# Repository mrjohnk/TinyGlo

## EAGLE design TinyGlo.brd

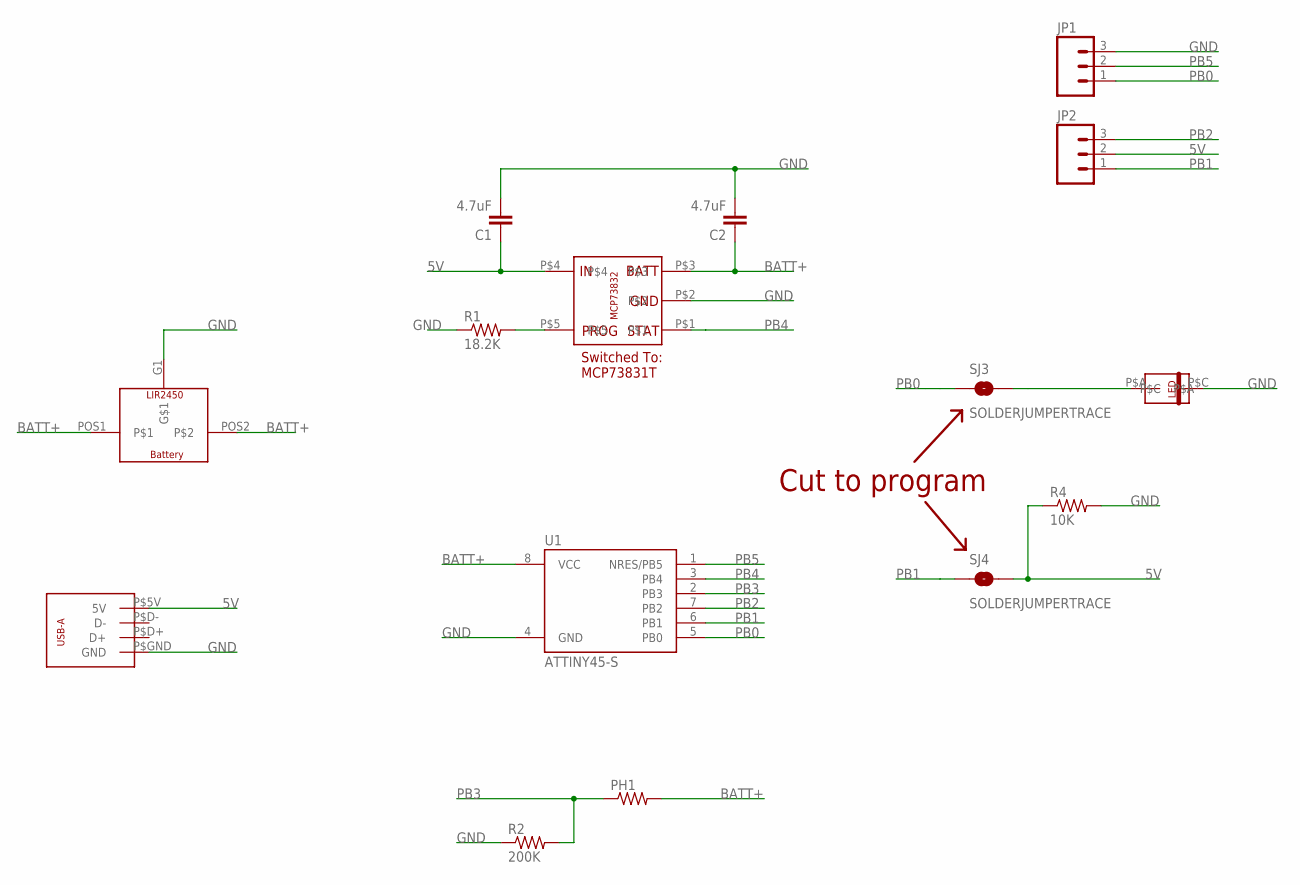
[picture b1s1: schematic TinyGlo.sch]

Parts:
C1, C2: 4.7uF; 0603-CAP
JP1, JP2: M03LOCK; 1X03_LOCK
PH1: RESISTOR0805-RES; 0805
R1: 18.2K; 0603-RES
R2: 200K; 0603-RES
R4: 10K; 0603-RES
SJ3, SJ4: SOLDERJUMPERTRACE; SJ_2S-TRACE
U1: ATTINY45-S; SOIC8_EIAJ_208MIL
U$1: LIPOBATTCHG-MCP73832T-2DFI/OT
U$2: LIR2450_SMD_BATT_BK-5033
U$3: USB-A_PCB_TRACES
U$4: PLCC-2_LED

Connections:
5V: C1.1, JP2.2, R4.1, SJ4.2, U$1.P$4, U$3.P$5V (5V)
BATT+: C2.1, PH1.2, U1.8 (VCC), U$1.P$3, U$2.POS1, U$2.POS2
GND: C1.2, C2.2, JP1.3, R1.1, R2.1, R4.2, U1.4 (GND), U$1.P$2, U$2.G1, U$3.P$GND (GND), U$4.P$C
unnamed: R1.2, U$1.P$5
unnamed: SJ3.2, U$4.P$A
PB0: JP1.1, SJ3.1, U1.5 (PB0)
PB1: JP2.1, SJ4.1, U1.6 (PB1)
PB2: JP2.3, U1.7 (PB2)
PB3: PH1.1, R2.2, U1.2 (PB3)
PB4: U1.3 (PB4), U$1.P$1
PB5: JP1.2, U1.1 (NRES/PB5)

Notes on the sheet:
Cut to program
Switched To: MCP73831T

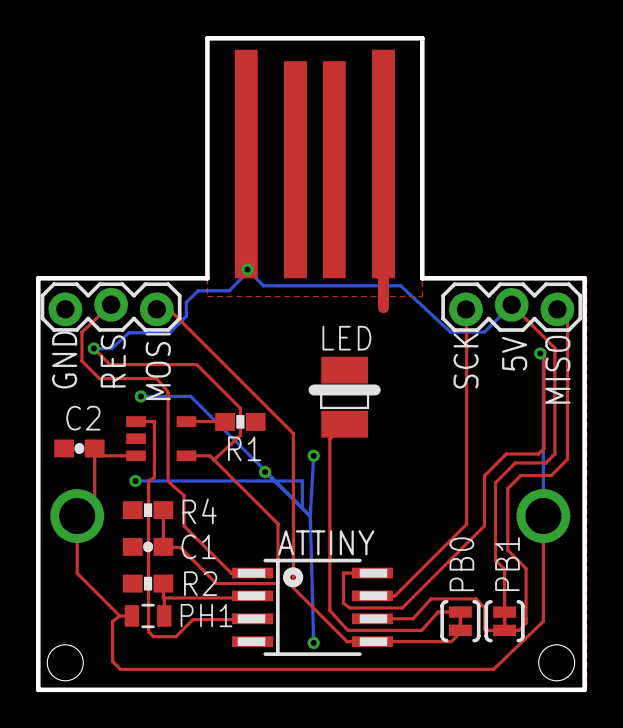
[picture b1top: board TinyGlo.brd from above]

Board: 2 copper layers, 30.4 x 36.2 mm, 15 parts (1 on the bottom side), 11 nets.

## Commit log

2014-03-24 TinyGlo
2014-09-12 Eagle design files
2014-09-12 Bill Of Materials

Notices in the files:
parts and their libraries:
SparkFun-Capacitors: Licensing: CC v3.0 Share-Alike You are welcome to use this library for commercial purposes.
